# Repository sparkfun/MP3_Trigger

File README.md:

MP3 Trigger
============

[*MP3 Trigger (WIG-13720)*](https://www.sparkfun.com/products/13720)

 The MP3 Trigger board is built to make it MP3 sound integration easier than ever. 
 The board has 18 external trigger pins that will directly trigger pre-selected MP3 tracks, and a full-duplex serial control port that provides full transport control, remote triggering for up to 256 tracks, and fast real-time volume control. 
 
Repository Contents
-------------------
* **/Hardware** - All Eagle design files (.brd, .sch)
* **/Production** - Production files

Documentation
--------------
* **[Hookup Guide](https://learn.sparkfun.com/tutorials/mp3-trigger-hookup-guide-v24)** - Basic hookup guide for the MP3 Trigger.
* **[SparkFun Fritzing repo](https://github.com/sparkfun/Fritzing_Parts)** - Fritzing diagrams for SparkFun products.
* **[SparkFun 3D Model repo](https://github.com/sparkfun/3D_Models)** - 3D models of SparkFun products. 
* **[SparkFun Graphical Datasheets](https://github.com/sparkfun/Graphical_Datasheets)** -Graphical Datasheets for various SparkFun products.

License Information
-------------------

This product is _**open source**_! 

Please review the LICENSE.md file for license information. 

If you have any questions or concerns on licensing, please contact techsupport@sparkfun.com.

Distributed as-is; no warranty is given.

- Your friends at SparkFun.

_**Note:** This product is a collaboration with Robertsonics. A portion of each sales goes back to them for product support and continued development._

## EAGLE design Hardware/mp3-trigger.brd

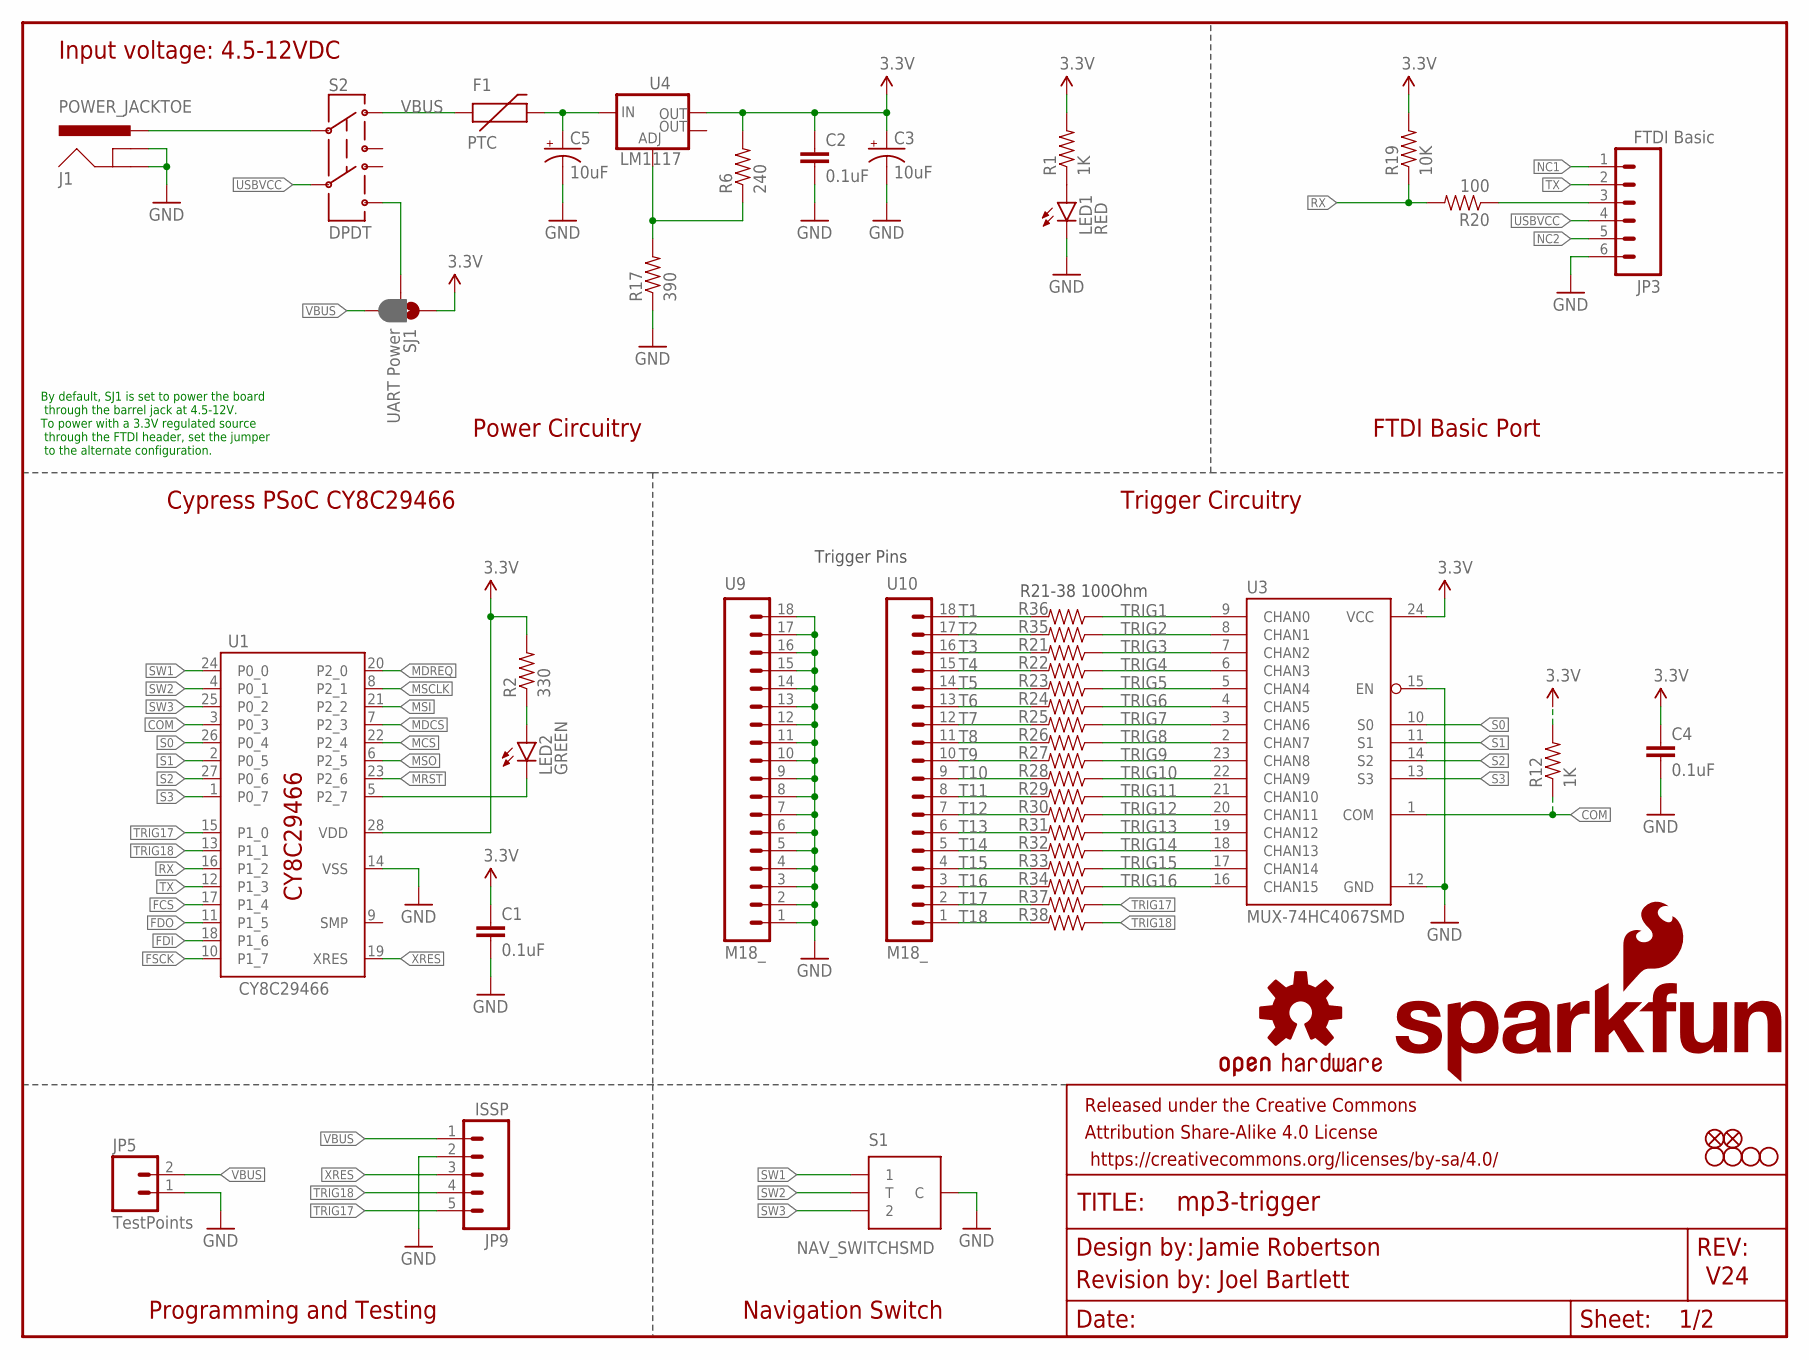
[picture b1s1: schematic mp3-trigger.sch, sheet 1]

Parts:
C1, C2, C4: 0.1uF; 0603-CAP
C3, C5: 10uF; EIA3216
F1: PTC; PTC-1206
FRAME3: FRAME-LETTER; CREATIVE_COMMONS
J1: POWER_JACKTOE; POWER_JACK_SMD_OVERPASTE_TOE
JP3: FTDI Basic; 1X06
JP5: TestPoints; 1X02
JP6, JP7: FIDUCIAL1X2; FIDUCIAL-1X2
JP9: ISSP; 1X05
LED1: RED; LED-1206
LED2: GREEN; LED-1206
LOGO3: OSHW-LOGOM; OSHW-LOGO-M
R1, R12: 1K; 0603-RES
R2: 330; 0603-RES
R6: 240; 0603-RES
R17: 390; 0603-RES
R19: 10K; 0603-RES
R20, R21, R22, R23, R24, R25, R26, R27, R28, R29, R30, R31, R32, R33, R34, R35, R36, R37, R38: 100; 0603-RES
S1: NAV_SWITCHSMD; NAV_SWITCH
S2: DPDT; AYZ0202
SJ1: UART Power; PAD-JUMPER-3-2OF3_NC_BY_PASTE_YES_SILK_FULL_BOX
U1: CY8C29466; SOIC-28
U3: MUX-74HC4067SMD; SSOP24
U4: LM1117; SOT223
U9, U10: M18_; 1X18
U$1: SFE_LOGO_NAME_FLAME.2_INCH; SFE_LOGO_NAME_FLAME_.2
U$12, U$13, U$14, U$15: STAND-OFF

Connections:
3.3V: C1.1, C2.1, C3.A (+), C4.1, R1.2, R2.2, R6.2, R12.2, R19.2, SJ1.1, U1.28 (VDD), U3.24 (VCC), U4.2 (OUT); also elsewhere on the board
COM: R12.1, U1.3 (P0_3), U3.1 (COM)
FCS: U1.17 (P1_4); also elsewhere on the board
FDI: U1.18 (P1_6); also elsewhere on the board
FDO: U1.11 (P1_5); also elsewhere on the board
FSCK: U1.10 (P1_7); also elsewhere on the board
GND: C1.2, C2.2, C3.C (-), C4.2, C5.C (-), J1.GND (GNDBREAK), J1.P$4 (GND), JP3.6, JP5.1, JP9.2, LED1.C, R17.1, S1.C, U1.14 (VSS), U3.12 (GND), U3.15 (EN), U9.1, U9.2, U9.3, U9.4, U9.5, U9.6, U9.7, U9.8, U9.9, U9.10, U9.11, U9.12, U9.13, U9.14, U9.15, U9.16, U9.17, U9.18; also elsewhere on the board
MCS: U1.22 (P2_4); also elsewhere on the board
MDCS: U1.7 (P2_3); also elsewhere on the board
MDREQ: U1.20 (P2_0); also elsewhere on the board
MRST: U1.23 (P2_6); also elsewhere on the board
MSCLK: U1.8 (P2_1); also elsewhere on the board
MSI: U1.21 (P2_2); also elsewhere on the board
MSO: U1.6 (P2_5); also elsewhere on the board
unnamed: R6.1, R17.2, U4.1 (ADJ)
unnamed: LED1.A, R1.1
unnamed: LED2.A, R2.1
unnamed: LED2.C, U1.5 (P2_7)
unnamed: J1.VIN0 (PWR), S2.2
unnamed: C5.A (+), F1.2, U4.3 (IN)
unnamed: S2.6, SJ1.2
NC1: JP3.1
NC2: JP3.5
RX: R19.1, R20.2, U1.16 (P1_2)
RX-I: JP3.3, R20.1
S0: U1.26 (P0_4), U3.10 (S0)
S1: U1.2 (P0_5), U3.11 (S1)
S2: U1.27 (P0_6), U3.14 (S2)
S3: U1.1 (P0_7), U3.13 (S3)
SW1: S1.1, U1.24 (P0_0)
SW2: S1.T, U1.4 (P0_1)
SW3: S1.2, U1.25 (P0_2)
T1: R36.2, U10.18
T2: R35.2, U10.17
T3: R21.2, U10.16
T4: R22.2, U10.15
T5: R23.2, U10.14
T6: R24.2, U10.13
T7: R25.2, U10.12
T8: R26.2, U10.11
T9: R27.2, U10.10
T10: R28.2, U10.9
T11: R29.2, U10.8
T12: R30.2, U10.7
T13: R31.2, U10.6
T14: R32.2, U10.5
T15: R33.2, U10.4
T16: R34.2, U10.3
T17: R37.2, U10.2
T18: R38.2, U10.1
TRIG1: R36.1, U3.9 (CHAN0)
TRIG2: R35.1, U3.8 (CHAN1)
TRIG3: R21.1, U3.7 (CHAN2)
TRIG4: R22.1, U3.6 (CHAN3)
TRIG5: R23.1, U3.5 (CHAN4)
TRIG6: R24.1, U3.4 (CHAN5)
TRIG7: R25.1, U3.3 (CHAN6)
TRIG8: R26.1, U3.2 (CHAN7)
TRIG9: R27.1, U3.23 (CHAN8)
TRIG10: R28.1, U3.22 (CHAN9)
TRIG11: R29.1, U3.21 (CHAN10)
TRIG12: R30.1, U3.20 (CHAN11)
TRIG13: R31.1, U3.19 (CHAN12)
TRIG14: R32.1, U3.18 (CHAN13)
TRIG15: R33.1, U3.17 (CHAN14)
TRIG16: R34.1, U3.16 (CHAN15)
TRIG17: JP9.5, R37.1, U1.15 (P1_0)
TRIG18: JP9.4, R38.1, U1.13 (P1_1)
TX: JP3.2, U1.12 (P1_3)
USBVCC: JP3.4, S2.5
VBUS: F1.1, JP5.2, JP9.1, S2.1, SJ1.3
XRES: JP9.3, U1.19 (XRES)

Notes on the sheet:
R21-38 100Ohm
Trigger Pins
Jamie Robertson
Revision by: Joel Bartlett
V24
FTDI Basic Port
Power Circuitry
Trigger Circuitry
Cypress PSoC CY8C29466
Navigation Switch
Programming and Testing
Input voltage: 4.5-12VDC
By default, SJ1 is set to power the board through the barrel jack at 4.5-12V. To power with a 3.3V regulated source through the FTDI header, set the jumper to the alternate configuration.

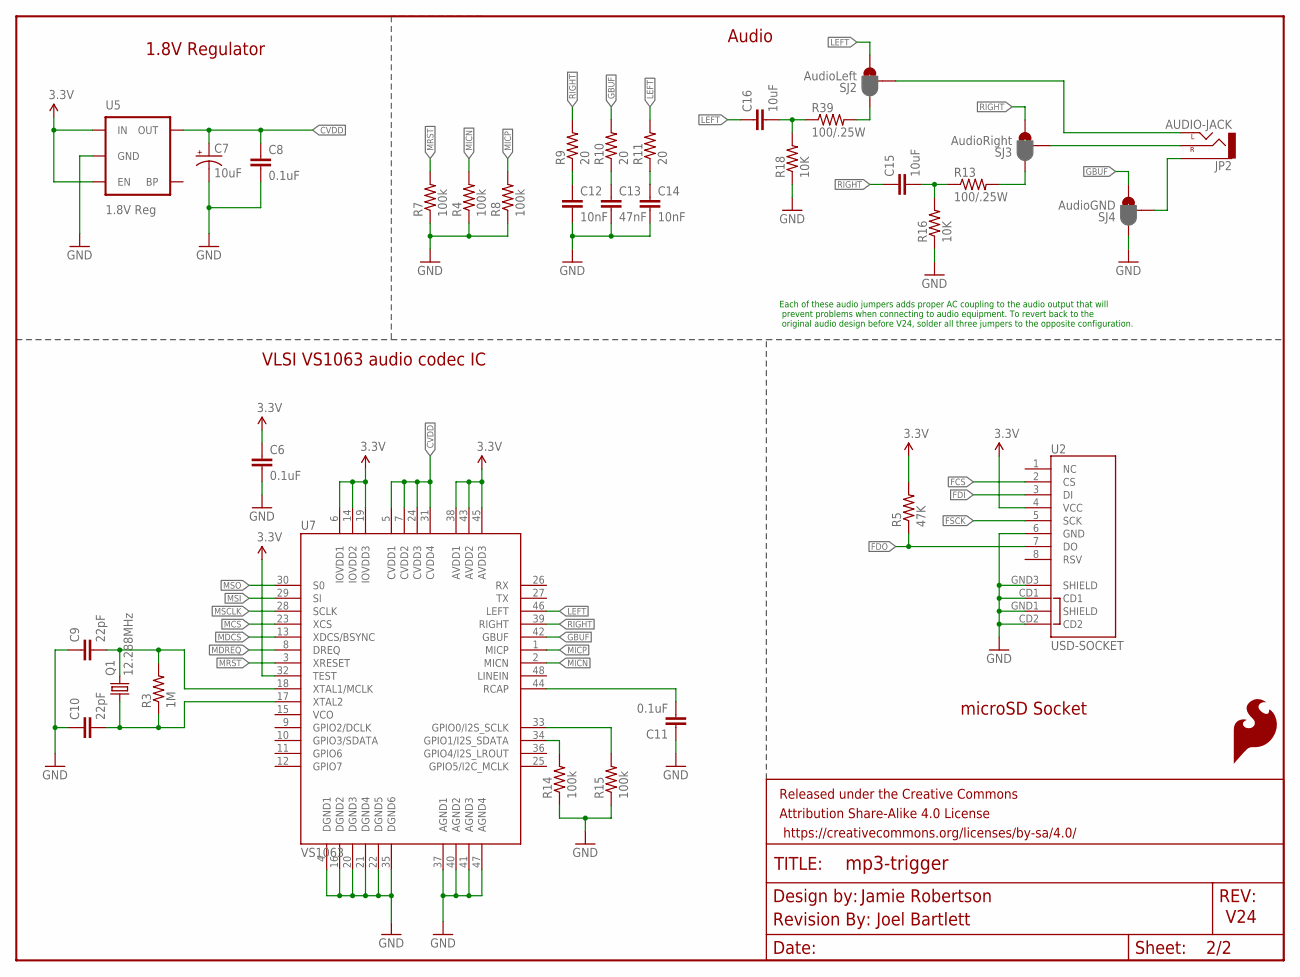
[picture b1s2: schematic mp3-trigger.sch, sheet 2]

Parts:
C6, C8, C11: 0.1uF; 0603-CAP
C7: 10uF; EIA3216
C9, C10: 22pF; 0603-CAP
C12, C14: 10nF; 0603-CAP
C13: 47nF; 0603-CAP
C15, C16: 10uF; 0603-CAP
FRAME1: FRAME-LETTERNO_PACKAGE; DUMMY
JP2: AUDIO-JACK; AUDIO-JACK-3.5MM-SMD
LOGO1: SFE_LOGO_FLAME.3_INCH; SFE_LOGO_FLAME_.3
Q1: 12.288MHz; CRYSTAL-SMD-5X3
R3: 1M; 0603-RES
R4, R7, R8, R14, R15: 100k; 0603-RES
R5: 47K; 0603-RES
R9, R10, R11: 20; 0603-RES
R13, R39: 100/.25W; 0603-RES
R16, R18: 10K; 0603-RES
SJ2: AudioLeft; PAD-HUMPER-3-1&2_NC_BY_PASTE_YES_SILK_FULL_BOX
SJ3: AudioRight; PAD-HUMPER-3-1&2_NC_BY_PASTE_YES_SILK_FULL_BOX
SJ4: AudioGND; PAD-HUMPER-3-1&2_NC_BY_PASTE_YES_SILK_FULL_BOX
U2: USD-SOCKET; MICROSD_1:1
U5: 1.8V Reg; SC70
U7: VS1063; LQFP-48
U$4: REVISION

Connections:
3.3V: C6.1, R5.2, U2.4 (VCC), U5.1 (IN), U5.3 (EN), U7.6 (IOVDD1), U7.14 (IOVDD2), U7.19 (IOVDD3), U7.32 (TEST), U7.38 (AVDD1), U7.43 (AVDD2), U7.45 (AVDD3); also elsewhere on the board
CVDD: C7.A (+), C8.1, U5.5 (OUT), U7.5 (CVDD1), U7.7 (CVDD2), U7.24 (CVDD3), U7.31 (CVDD4)
FCS: U2.2 (CS); also elsewhere on the board
FDI: U2.3 (DI); also elsewhere on the board
FDO: R5.1, U2.7 (DO); also elsewhere on the board
FSCK: U2.5 (SCK); also elsewhere on the board
GBUF: R10.2, SJ4.3, U7.42 (GBUF)
GND: C6.2, C7.C (-), C8.2, C9.1, C10.1, C11.1, C12.2, C13.2, C14.2, R4.1, R7.1, R8.1, R14.1, R15.1, R16.1, R18.1, SJ4.1, U2.6 (GND), U2.CD1, U2.CD2, U2.GND1 (SHIELD), U2.GND3 (SHIELD), U5.2 (GND), U7.4 (DGND1), U7.16 (DGND2), U7.20 (DGND3), U7.21 (DGND4), U7.22 (DGND5), U7.35 (DGND6), U7.37 (AGND1), U7.40 (AGND2), U7.41 (AGND3), U7.47 (AGND4); also elsewhere on the board
LEFT: C16.1, R11.2, SJ2.3, U7.46 (LEFT)
MCS: U7.23 (XCS); also elsewhere on the board
MDCS: U7.13 (XDCS/BSYNC); also elsewhere on the board
MDREQ: U7.8 (DREQ); also elsewhere on the board
MICN: R4.2, U7.2 (MICN)
MICP: R8.2, U7.1 (MICP)
MRST: R7.2, U7.3 (XRESET); also elsewhere on the board
MSCLK: U7.28 (SCLK); also elsewhere on the board
MSI: U7.29 (SI); also elsewhere on the board
MSO: U7.30 (S0); also elsewhere on the board
unnamed: JP2.SLEEVE, SJ4.2
unnamed: C9.2, Q1.3 (2), R3.2, U7.18 (XTAL1/MCLK)
unnamed: C10.2, Q1.1, R3.1, U7.17 (XTAL2)
unnamed: JP2.RING (RIGHT), SJ3.2
unnamed: R13.2, SJ3.1
unnamed: C15.2, R13.1, R16.2
unnamed: R14.2, U7.34 (GPIO1/I2S_SDATA)
unnamed: C11.2, U7.44 (RCAP)
unnamed: C14.1, R11.1
unnamed: C13.1, R10.1
unnamed: C12.1, R9.1
unnamed: R15.2, U7.33 (GPIO0/I2S_SCLK)
unnamed: JP2.TIP (LEFT), SJ2.2
unnamed: R39.2, SJ2.1
unnamed: C16.2, R18.2, R39.1
RIGHT: C15.1, R9.2, SJ3.3, U7.39 (RIGHT)

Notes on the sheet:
Jamie Robertson
Joel Bartlett
V24
VLSI VS1063 audio codec IC
microSD Socket
Audio
1.8V Regulator
Each of these audio jumpers adds proper AC coupling to the audio output that will prevent problems when connecting to audio equipment. To revert back to the original audio design before V24, solder all three jumpers to the opposite configuration.

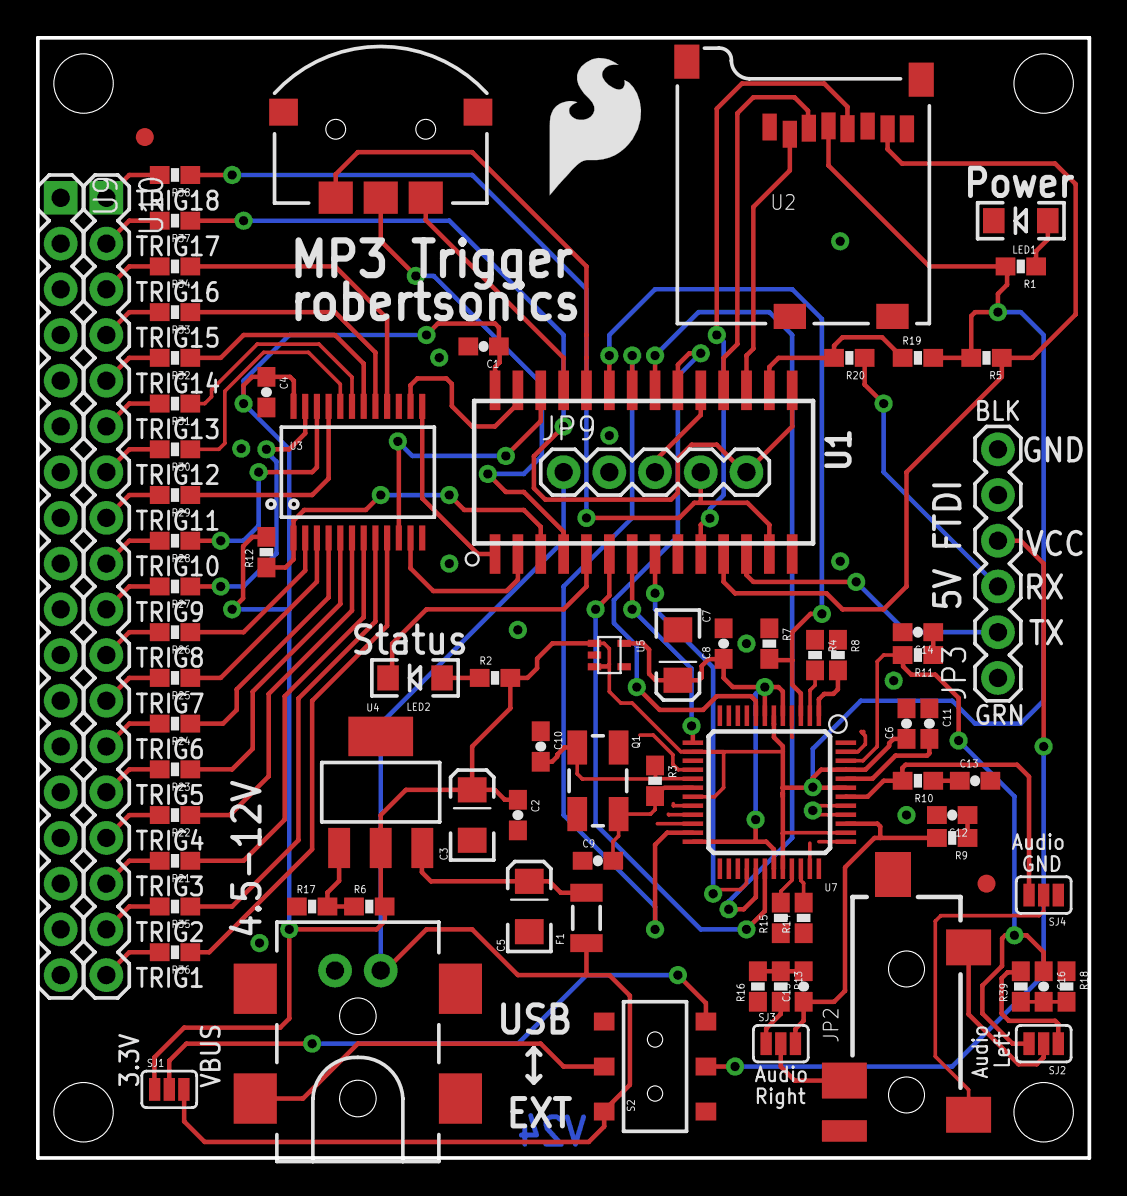
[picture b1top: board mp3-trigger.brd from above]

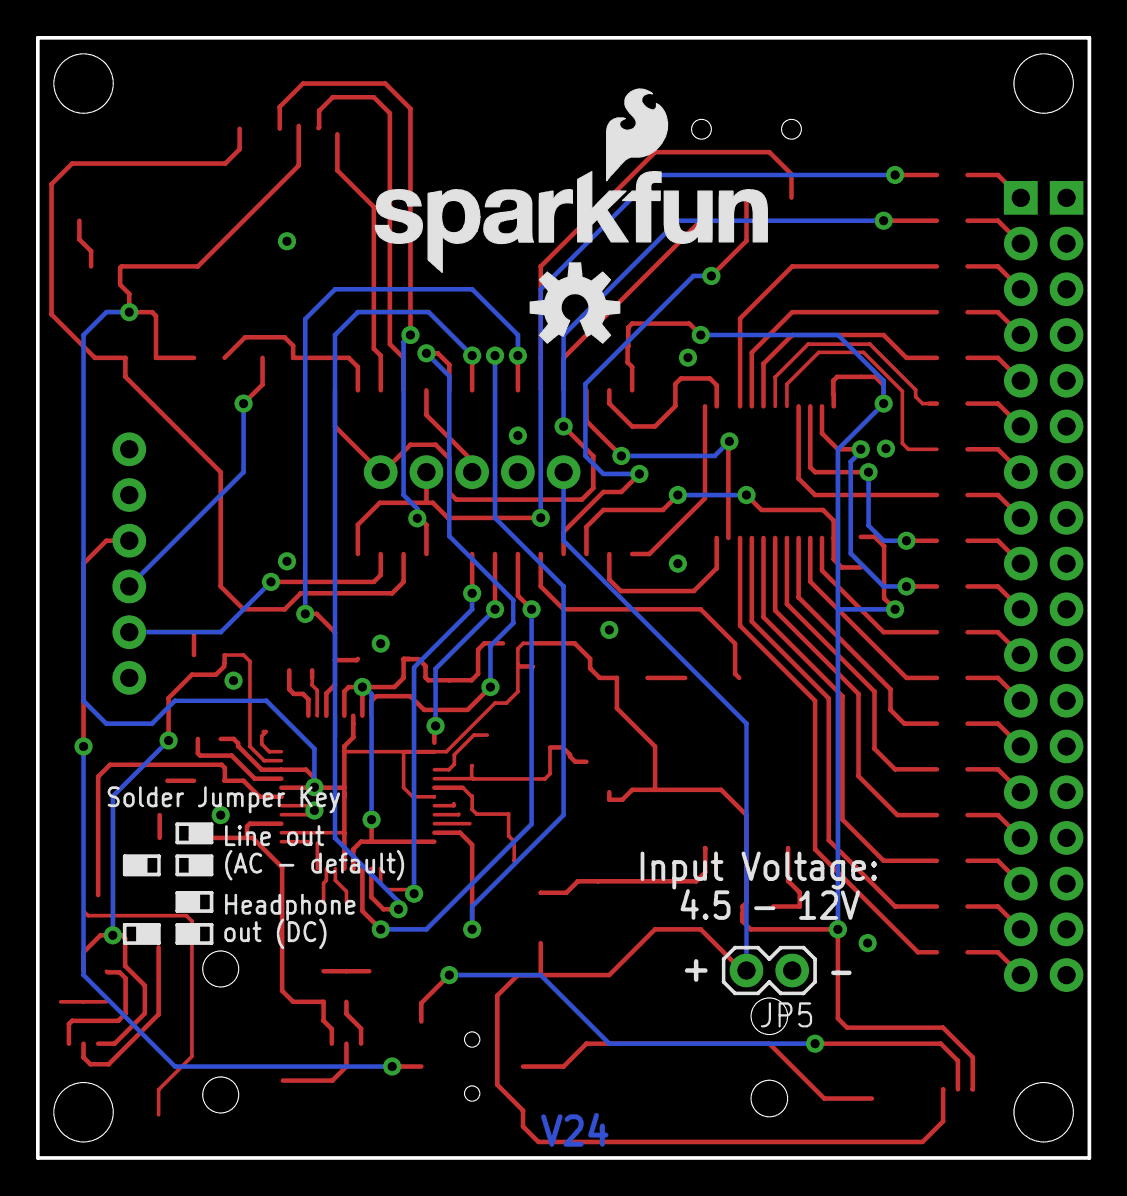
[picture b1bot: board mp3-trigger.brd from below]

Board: 2 copper layers, 58.4 x 62.2 mm, 90 parts (3 on the bottom side), 91 nets.

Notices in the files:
parts and their libraries:
SparkFun-Aesthetics: Licensing: Creative Commons ShareAlike 4.0 International - https://creativecommons.org/licenses/by-sa/4.0
SparkFun-Aesthetics: Released under the Creative Commons Attribution Share-Alike 4.0 License
SparkFun-Aesthetics: https://creativecommons.org/licenses/by-sa/4.0
